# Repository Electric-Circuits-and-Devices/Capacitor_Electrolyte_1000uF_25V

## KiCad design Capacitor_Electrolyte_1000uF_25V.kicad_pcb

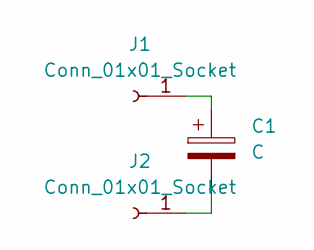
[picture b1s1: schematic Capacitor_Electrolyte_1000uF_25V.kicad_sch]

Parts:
C1: C; CP_Radial_D10.0mm_P5.00mm
J1, J2: Conn_01x01_Socket; MountingHole_2.5mm_Pad

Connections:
unnamed: C1.1, J1.1
unnamed: C1.2, J2.1

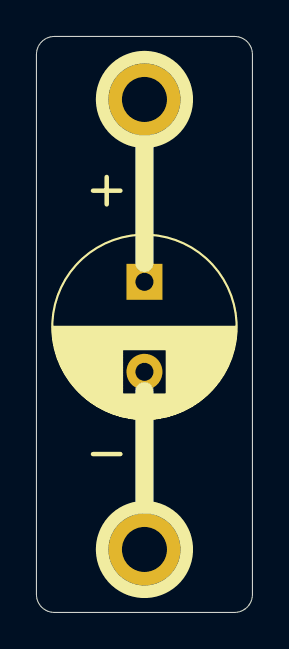
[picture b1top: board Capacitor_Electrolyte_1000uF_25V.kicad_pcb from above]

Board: 2 copper layers, 12.0 x 32.0 mm, 3 parts (0 on the bottom side), 2 nets.
